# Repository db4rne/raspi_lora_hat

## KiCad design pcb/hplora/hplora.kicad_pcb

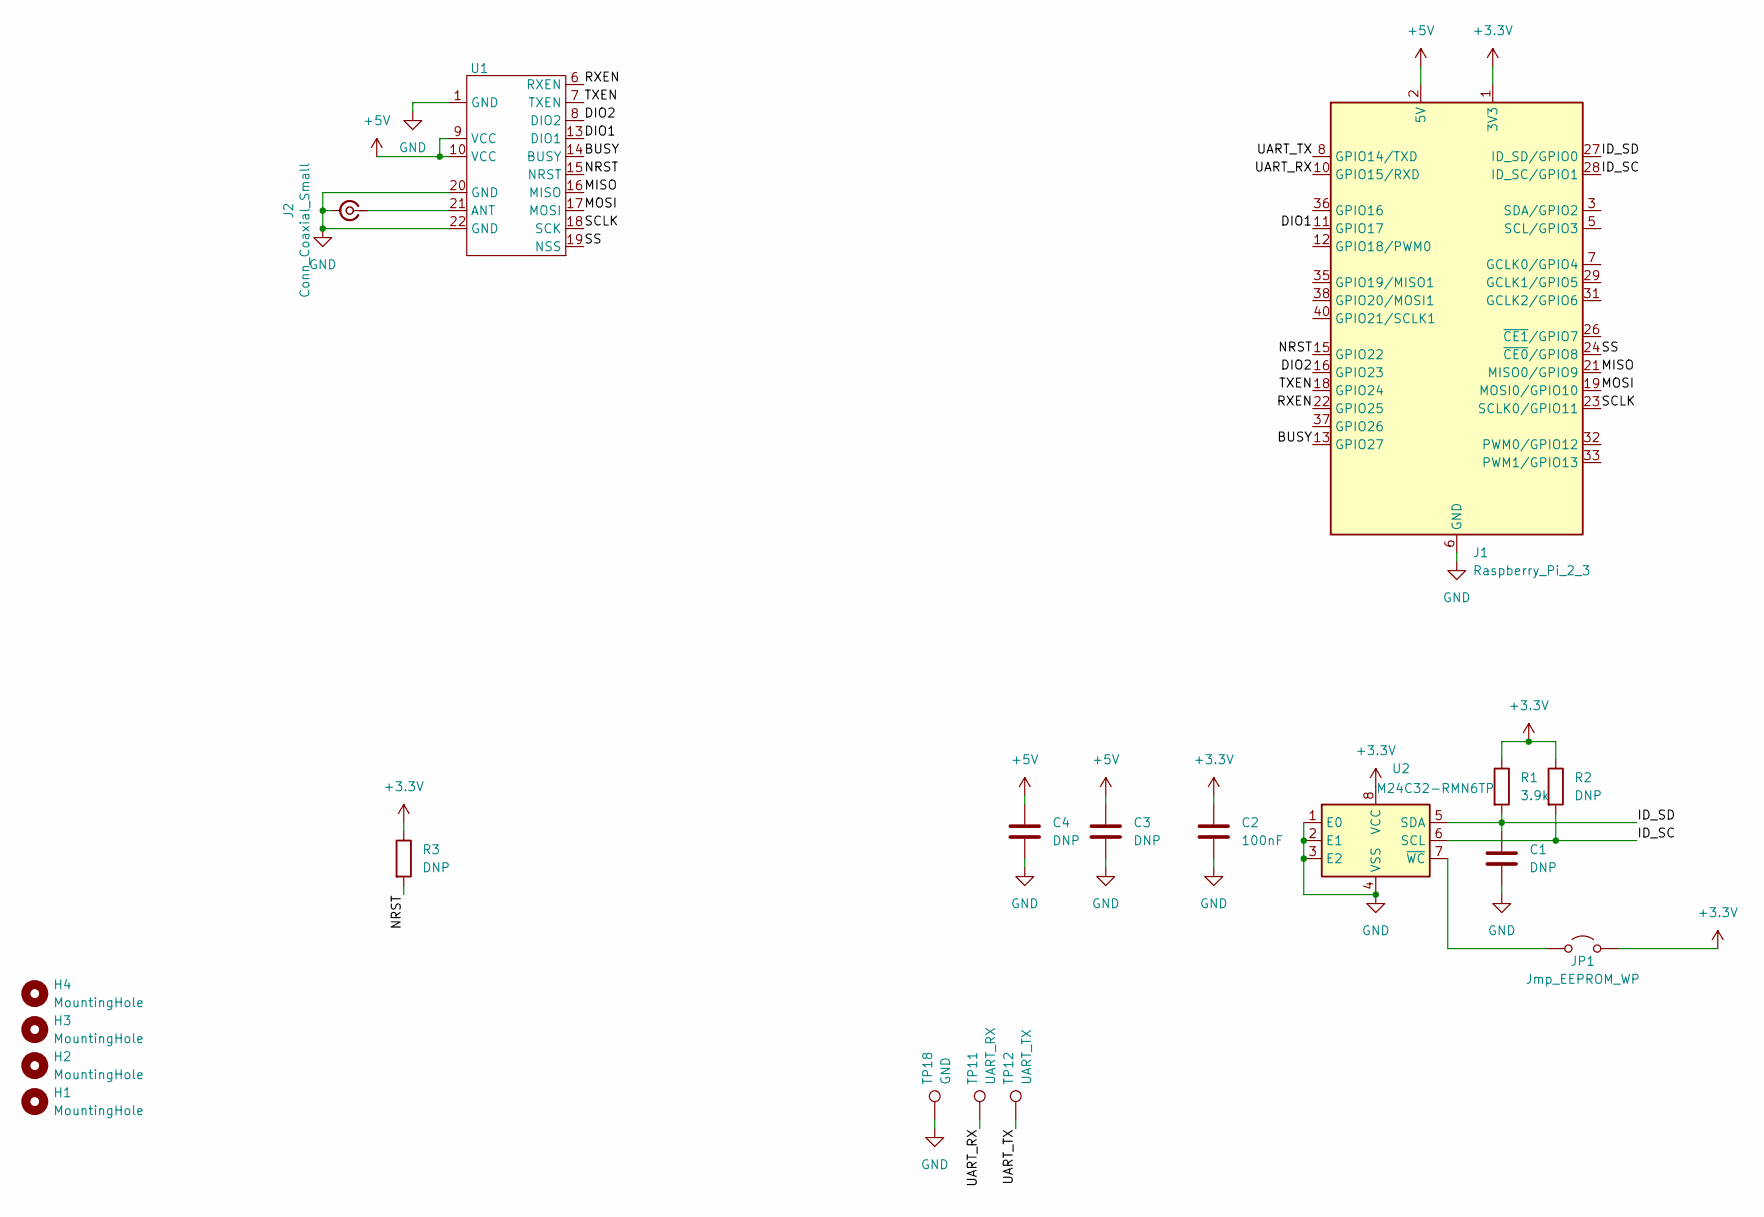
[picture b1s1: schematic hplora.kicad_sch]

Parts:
C1: DNP; C_0603_1608Metric_Pad1.08x0.95mm_HandSolder
C2: 100nF; C_0603_1608Metric_Pad1.08x0.95mm_HandSolder
C3: DNP; C_0603_1608Metric
C4: DNP; C_1206_3216Metric
H1, H2, H3, H4: MountingHole; MountingHole_2.7mm_M2.5
J1: Raspberry_Pi_2_3; PinSocket_2x20_P2.54mm_Vertical_SMD
J2: Conn_Coaxial_Small; SMA_Amphenol_132289_EdgeMount
JP1: Jmp_EEPROM_WP; SolderJumper-2_P1.3mm_Open_RoundedPad1.0x1.5mm
R1: 3.9k; R_0603_1608Metric
R2, R3: DNP; R_0603_1608Metric
TP11: UART_RX; TestPoint_Pad_D1.0mm
TP12: UART_TX; TestPoint_Pad_D1.0mm
TP18: GND; TestPoint_Pad_D1.0mm
U1: E22-xxxM33S
U2: M24C32-RMN6TP; SOIC-8_3.9x4.9mm_P1.27mm

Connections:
+3.3V: C2.1, J1.1 (3V3), J1.17 (3V3), JP1.2 (B), R1.1, R2.1, R3.1, U2.8 (VCC)
+5V: C3.1, C4.1, J1.2 (5V), J1.4 (5V), U1.9 (VCC), U1.10 (VCC)
/BUSY: J1.13 (GPIO27), U1.14 (BUSY)
/DIO1: J1.11 (GPIO17), U1.13 (DIO1)
/DIO2: J1.16 (GPIO23), U1.8 (DIO2)
/ID_SC: J1.28 (ID_SC/GPIO1), R2.2, U2.6 (SCL)
/ID_SD: C1.1, J1.27 (ID_SD/GPIO0), R1.2, U2.5 (SDA)
/MISO: J1.21 (MISO0/GPIO9), U1.16 (MISO)
/MOSI: J1.19 (MOSI0/GPIO10), U1.17 (MOSI)
/NRST: J1.15 (GPIO22), R3.2, U1.15 (NRST)
/RXEN: J1.22 (GPIO25), U1.6 (RXEN)
/SCLK: J1.23 (SCLK0/GPIO11), U1.18 (SCK)
/SS: J1.24 (~CE0/GPIO8), U1.19 (NSS)
/TXEN: J1.18 (GPIO24), U1.7 (TXEN)
/UART_RX: J1.10 (GPIO15/RXD), TP11.1
/UART_TX: J1.8 (GPIO14/TXD), TP12.1
GND: C1.2, C2.2, C3.2, C4.2, J1.6 (GND), J1.9 (GND), J1.14 (GND), J1.20 (GND), J1.25 (GND), J1.30 (GND), J1.34 (GND), J1.39 (GND), J2.2 (Ext), TP18.1, U1.1 (GND), U1.2 (GND), U1.3 (GND), U1.4 (GND), U1.5 (GND), U1.11 (GND), U1.12 (GND), U1.20 (GND), U1.22 (GND), U2.1 (E0), U2.2 (E1), U2.3 (E2), U2.4 (VSS)
unnamed: J2.1 (In), U1.21 (ANT)
unnamed: JP1.1 (A), U2.7 (~WC)

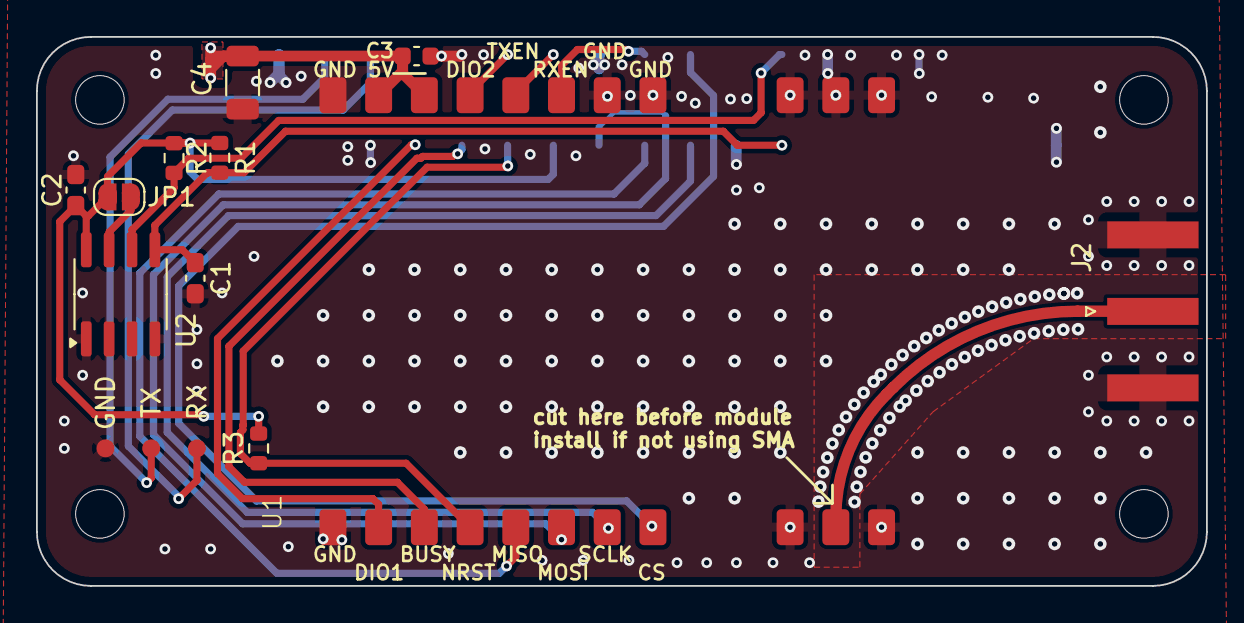
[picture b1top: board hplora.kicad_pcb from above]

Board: 2 copper layers, 65.0 x 30.5 mm, 19 parts (1 on the bottom side), 19 nets.

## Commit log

2024-12-05 initial commit of version 1
